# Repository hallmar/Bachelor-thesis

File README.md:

# Bachelor-thesis
This is the repository for my bachelor thesis at the University of Ravensburg Weingarten.

The thesis is around phase modulation synthesis and the hardware platform that I designed around synthesizing PM sounds.

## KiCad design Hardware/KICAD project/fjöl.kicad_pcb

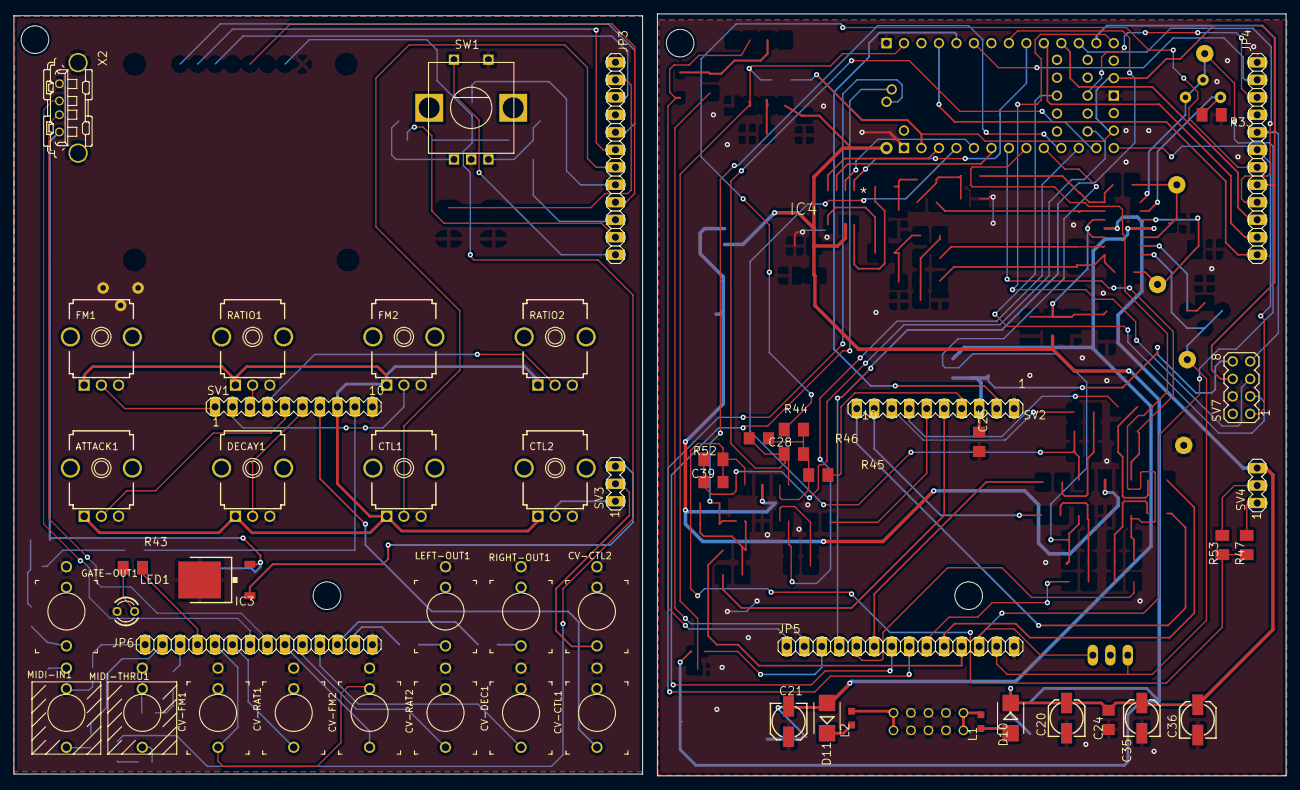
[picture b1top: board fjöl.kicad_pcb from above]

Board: 2 copper layers, 184.8 x 110.7 mm, 103 parts (0 on the bottom side), 84 nets.

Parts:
@HOLE0, @HOLE1, @HOLE5, @HOLE6: (no value)
ATTACK1: 50k-lin; 9MM_SNAP-IN_POT
C20, C21, C27, C33, C35, C36, C37, C38, C52: 100µ; 153CLV-0505
C22, C23, C24, C25, C26, C29, C32, C34, C40, C53: 100n; C1206
C28, C39: 1n; C1206
C30, C31: 10n; C1206
CTL1, CTL2: 50k lin; 9MM_SNAP-IN_POT
CV-CTL1, CV-CTL2: THONKICONNNEW; WQP-PJ301M-12_JACK
CV-DEC1: THONKICONNNEW; WQP-PJ301M-12_JACK
CV-FM1, CV-FM2: THONKICONNNEW; WQP-PJ301M-12_JACK
CV-RAT1, CV-RAT2: THONKICONNNEW; WQP-PJ301M-12_JACK
D10, D11: STPS1L30U; SMB
DECAY1: 50k-lin; 9MM_SNAP-IN_POT
FM1, FM2: 50k-lin; 9MM_SNAP-IN_POT
GAINRIGHT1: 10k; BOURNS_3362P_TRIMMER
GATE-OUT1: THONKICONNNEW; WQP-PJ301M-12_JACK
GND1: 2,54_1,0
IC1, IC3: 78DT; TO252
IC6: LM4040B10; DBZ_R-PDSO-G3
IC9: REG1117; SOT223
JP3, JP4: PINHD-1X12; 1X12
JP5, JP6: PINHD-1X14; 1X14
L1, L2, L3: BLM21PG221SN1D; L2012C
L4, L5, L6, L7: BLM21AG102SN1D; L2012C
L-OUT1: 2,54_1,0
LED1: LED3MM
LEFT-OUT1: THONKICONNNEW; WQP-PJ301M-12_JACK
MIDI-IN1: THONKI-STEREO; WQP-PJ366ST_JACK
MIDI-THRU1: THONKI-STEREO; WQP-PJ366ST_JACK
R33, R35, R38, R40, R43: 1k; M1206
R36, R37: 330; M1206
R39, R48, R49, R50, R51: 10k; M1206
R41: 33; M1206
R42: 10; M1206
R44, R47: 200k; M1206
R45, R53: 100k; M1206
R46, R52: 66.5k; M1206
R-OUT1: 2,54_1,0
RATIO1, RATIO2: 50k-lin; 9MM_SNAP-IN_POT
RIGHT-OUT1: THONKICONNNEW; WQP-PJ301M-12_JACK
SV1, SV2: MA10-1
SV3, SV4, SV5: MA03-1
SV7: MA04-2
SW1: EC12E_SW; ALPS_EC12E_SW
T1: BC847; SOT23
TP1, TP2: 2,54_1,0
U$1: TEENSY40
U$3: OLED-1.3; OLED-1.3_-164-32
X1: 2510-; PAK100_2500-10
X2: KUSBVX

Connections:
5V_USB: C52.+, C53.1, IC3.2, R39.1, X2.1
+3.3V: JP4.8, SV7.6, U$1.3V3-1, U$1.3V3-2, U$1.ON/OFF
+3.3V-REG: C29.1, C32.1, C33.+, C34.1, IC9.2
+12V: C20.+, C22.1, C24.1, C35.+, C36.+, D10.C, IC1.1, SV4.3
+12V-F: IC3.1, SV3.3
-10V: C25.1, IC6.2, R35.2, SV2.3, SV7.8
/DSP/+5V: C26.1, C27.+, IC1.2, IC9.3, U$1.VIN
/DSP/-12V: C21.-, C23.2, C37.-, C38.-, D11.A, R35.1
/DSP/CS_ADC: SV7.3, U$1.29-TX7
/DSP/MISO: SV7.5, U$1.12-MIO/MQSL
/frontpanel/+3.3V_F: JP3.8, L3.2
/frontpanel/+3.3V_F1: L3.1, R41.1, R48.2, R49.2
/frontpanel/-10V_F: ATTACK1.1, CTL1.1, CTL2.1, DECAY1.1, FM1.1, FM2.1, RATIO1.1, RATIO2.1, SV1.8
/frontpanel/ATT-POT-F: ATTACK1.2, SV1.5
/frontpanel/CTL1-POT: JP4.7, R44.1
/frontpanel/CTL1-POT-F: CTL1.2, JP3.7
/frontpanel/CTL2-POT: R47.1, SV4.1
/frontpanel/CTL2-POT-F: CTL2.2, SV3.1
/frontpanel/CV-CTL1: R45.1, SV2.4
/frontpanel/CV-CTL1-F: CV-CTL1.P$1_TIP, SV1.7
/frontpanel/CV-CTL2: R53.1, SV4.2
/frontpanel/CV-CTL2-F: CV-CTL2.P$1_TIP, SV3.2
/frontpanel/CV-DEC-F: CV-DEC1.P$1_TIP, JP6.11
/frontpanel/CV-FM1-F: CV-FM1.P$1_TIP, JP6.5
/frontpanel/CV-FM2-F: CV-FM2.P$1_TIP, JP6.9
/frontpanel/CV-RAT1-F: CV-RAT1.P$1_TIP, JP6.6
/frontpanel/CV-RAT2-F: CV-RAT2.P$1_TIP, JP6.10
/frontpanel/DEC-POT-F: DECAY1.2, SV1.6
/frontpanel/ENC-A-F: JP3.11, R51.2
/frontpanel/ENC-B-F: JP3.10, R50.1
/frontpanel/ENC-SW-F: JP3.12, SW1.D
/frontpanel/FM1-POT-F: FM1.2, SV1.1
/frontpanel/FM2-POT-F: FM2.2, SV1.2
/frontpanel/GATE-F: R38.1, SV1.9
/frontpanel/GATE-LED-F: JP6.4, R43.1
/frontpanel/LEFT-OUT-F: JP6.13, R36.1
/frontpanel/MIDI-IN-L-F: JP6.2, L4.1
/frontpanel/MIDI-IN-R-F: JP6.1, L5.1
/frontpanel/MIDI-THRU-R-F: JP6.3, R42.1
/frontpanel/RAT1-POT-F: RATIO1.2, SV1.3
/frontpanel/RAT2-POT-F: RATIO2.2, SV1.4
/frontpanel/RIGHT-OUT-F: JP6.12, R37.1
CONTROL1: C28.2, R46.2, U$1.14-A0/TX3/S-PFI_OUT
CONTROL2: C39.2, R52.2, U$1.24-A10/TX6/SCL2
CS: JP4.9, U$1.10-CS/MQSR
D+: JP5.7, U$1.D+
D+_F: JP6.7, X2.3
D-: JP5.8, U$1.D-
D-_F: JP6.8, X2.2
DC: JP4.3, U$1.28-RX7
ENC-A: JP4.11, U$1.8-TX2/IN1
ENC-B: JP4.10, U$1.9-OUT1C
ENC-SW: JP4.12, U$1.2-OUT2
GATE: SV2.2, U$1.3-LRCLK2
GATE-LED: JP5.4, U$1.6-OUT1D
GND: ATTACK1.3, C30.1, C31.1, C40.1, C52.-, C53.2, CTL1.3, CTL2.3, CV-CTL1.P$2_SWITCH, CV-CTL1.P$3_SLEEVE, CV-CTL2.P$2_SWITCH, CV-CTL2.P$3_SLEEVE, CV-DEC1.P$2_SWITCH, CV-DEC1.P$3_SLEEVE, CV-FM1.P$2_SWITCH, CV-FM1.P$3_SLEEVE, CV-FM2.P$2_SWITCH, CV-FM2.P$3_SLEEVE, CV-RAT1.P$2_SWITCH, CV-RAT1.P$3_SLEEVE, CV-RAT2.P$2_SWITCH, CV-RAT2.P$3_SLEEVE, DECAY1.3, FM1.3, FM2.3, GATE-OUT1.P$3_SLEEVE, IC3.3, JP3.1, JP6.14, LED1.K, LEFT-OUT1.P$3_SLEEVE, MIDI-THRU1.P$3_SLEEVE, RATIO1.3, RATIO2.3, RIGHT-OUT1.P$3_SLEEVE, SV1.10, SW1.C, SW1.E, T1.2, X2.4, X2.M1, X2.M2
GND1: C20.-, C21.+, C22.2, C23.1, C24.2, C25.2, C26.2, C27.-, C29.2, C32.2, C33.-, C34.2, C35.-, C36.-, C37.+, C38.+, GND1.1, IC1.3, IC6.1, IC9.1, JP4.1, JP5.14, R33.2, SV2.1, SV5.2, SV7.4, U$1.GND1, U$1.GND2, U$1.GND3, X1.3, X1.4, X1.5, X1.6, X1.7, X1.8
LEFT-OUT: JP5.13, L-OUT1.1, SV5.1, U$3.2, U$3.3
MOSI: JP4.5, SV7.7, U$1.11-MOSI/CTX1
unnamed: C28.1, R44.2, R45.2, R46.1
unnamed: C30.2, R48.1, R51.1, SW1.A
unnamed: C31.2, R49.1, R50.2, SW1.B
unnamed: C39.1, R47.2, R52.1, R53.2
unnamed: C40.2, MIDI-IN1.P$3_SLEEVE
unnamed: D10.A, L1.2
unnamed: D11.C, L2.2
unnamed: GAINRIGHT1.1, R33.1
unnamed: GATE-OUT1.P$1_TIP, R40.2
unnamed: L1.1, X1.9, X1.10
unnamed: L2.1, X1.1, X1.2
unnamed: L4.2, MIDI-IN1.P$1_TIP
unnamed: L5.2, MIDI-IN1.P$2_SWITCH
unnamed: L6.1, R41.2
unnamed: L6.2, MIDI-THRU1.P$1_TIP
unnamed: L7.1, R42.2
unnamed: L7.2, MIDI-THRU1.P$2_SWITCH
unnamed: LED1.A, R43.2
unnamed: LEFT-OUT1.P$1_TIP, R36.2
unnamed: R37.2, RIGHT-OUT1.P$1_TIP
unnamed: R38.2, T1.1
unnamed: R39.2, R40.1, T1.3
RIGHT-OUT: GAINRIGHT1.2, GAINRIGHT1.3, JP5.12, R-OUT1.1, SV5.3
SCK: JP4.6, SV7.1, U$1.13-SCK/CRX1/LED
SWITCH: JP4.2, U$1.4-BCLK2

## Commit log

2021-02-19 Upload matlab code
2021-02-21 upload thesis
2021-02-21 update thesis
2021-02-21 final version of thesis
2021-02-24 Final update of thesis
